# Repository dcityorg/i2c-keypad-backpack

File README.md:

#### I²C Keypad Backpack Board

<div style="text-align: center;">
<div style="display: inline-block; margin-right: 5px;">

</div>
<div style="display: inline-block; margin-right: 5px;">

</div>
<div style="display: inline-block; margin-right: 5px;">

</div>
<div style="display: inline-block; margin-right: 5px;">

</div>
</div>

**[This link has details](https://www.dcity.org/portfolio/i2c-keypad-backpack-board) including**
* parts lists
* assembly instructions
* jumper configuration
* Arduino, Particle and Raspberry Pi software library usage
* Bare PC boards are available from OSHPark.

**License Information**
Open Source Hardware Design. Our License Information is [here](https://www.dcity.org/license-information/).

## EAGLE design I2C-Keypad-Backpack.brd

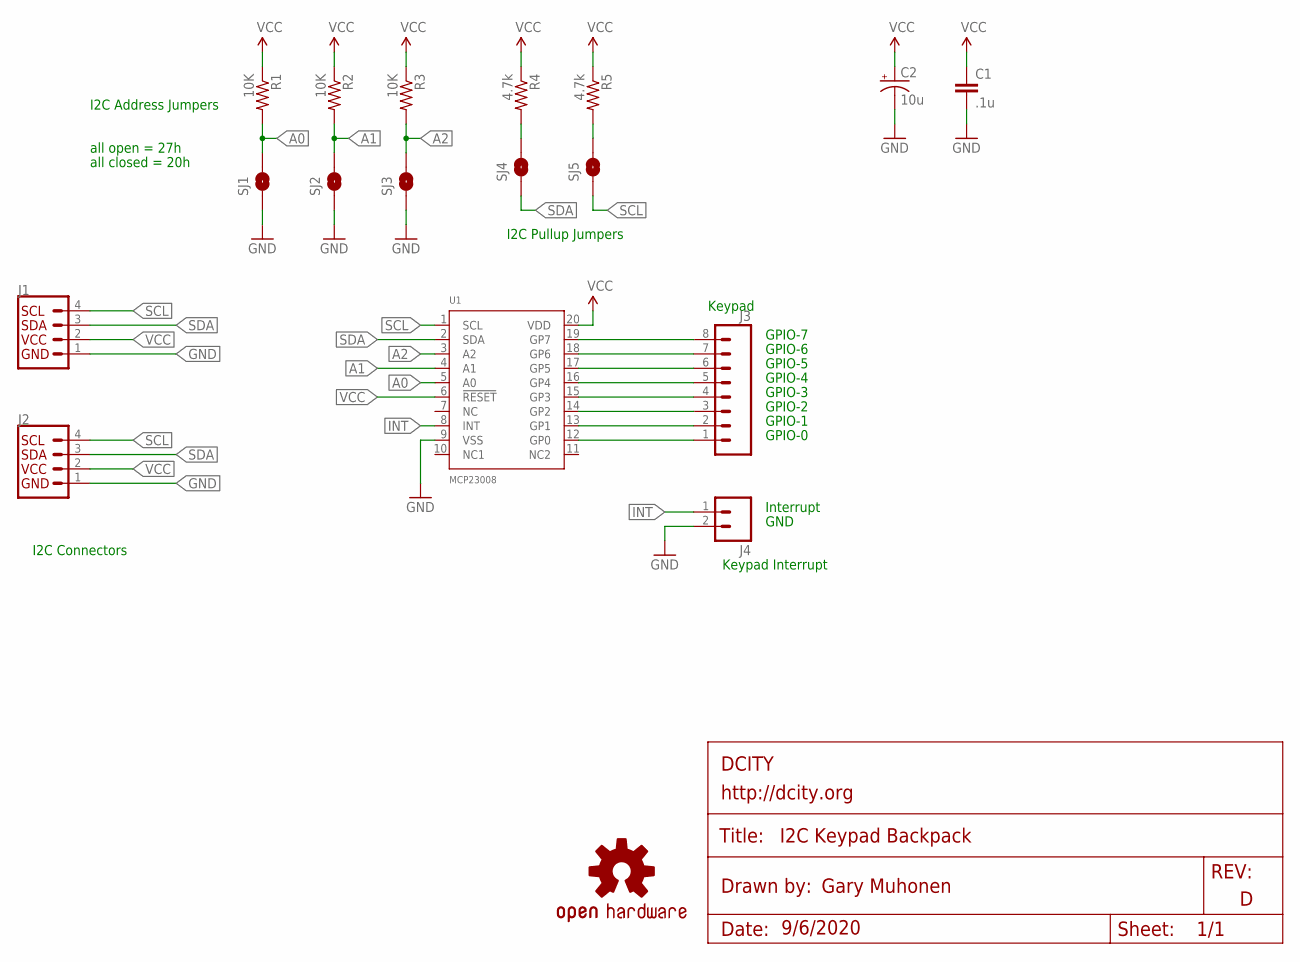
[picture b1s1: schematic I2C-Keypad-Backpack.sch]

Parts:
C1: .1u; 0805-CAP
C2: 10u; 0805-POL
J1, J2: QWIIC_RIGHT_ANGLE; JST04_1MM_RA
J3: M08LOCK; 1X08_LOCK
J4: M02LOCK; 1X02_LOCK
LOGO1: OSHW-LOGOS; OSHW-LOGO-S
R1, R2, R3: 10K; 0805-RES
R4, R5: 4.7k; 0805-RES
SJ1, SJ2, SJ3, SJ4, SJ5: SOLDERJUMPERNC; SJ_2S
U1: MCP23008; SSOP20-0.65-7.6X5.2MM

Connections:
A0: R1.2, SJ1.2, U1.5 (A0)
A1: R2.2, SJ2.2, U1.4 (A1)
A2: R3.2, SJ3.2, U1.3 (A2)
GND: C1.2, C2.-, J1.1, J2.1, J4.2, SJ1.1, SJ2.1, SJ3.1, U1.9 (VSS)
INT: J4.1, U1.8 (INT)
unnamed: R4.2, SJ4.2
unnamed: R5.2, SJ5.2
unnamed: J3.8, U1.19 (GP7)
unnamed: J3.7, U1.18 (GP6)
unnamed: J3.6, U1.17 (GP5)
unnamed: J3.5, U1.16 (GP4)
unnamed: J3.4, U1.15 (GP3)
unnamed: J3.3, U1.14 (GP2)
unnamed: J3.2, U1.13 (GP1)
unnamed: J3.1, U1.12 (GP0)
SCL: J1.4, J2.4, SJ5.1, U1.1 (SCL)
SDA: J1.3, J2.3, SJ4.1, U1.2 (SDA)
VCC: C1.1, C2.+, J1.2, J2.2, R1.1, R2.1, R3.1, R4.1, R5.1, U1.6 (!RESET), U1.20 (VDD)

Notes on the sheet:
all open = 27h
all closed = 20h
I2C Connectors
I2C Pullup Jumpers
I2C Address Jumpers
Keypad
GPIO-7
GPIO-6
GPIO-5
GPIO-4
GPIO-3
GPIO-2
GPIO-1
GPIO-0
Interrupt
GND
Keypad Interrupt

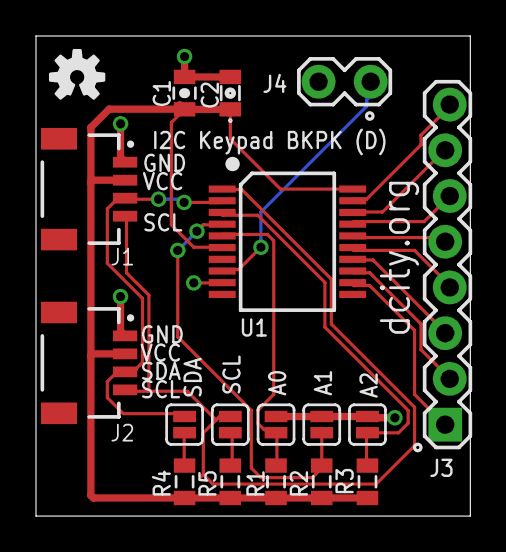
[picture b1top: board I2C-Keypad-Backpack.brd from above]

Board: 2 copper layers, 24.1 x 26.7 mm, 18 parts (0 on the bottom side), 18 nets.

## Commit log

2017-03-31 First commit - Rev B
2018-09-14 Rev C
2020-10-11 Rev D
